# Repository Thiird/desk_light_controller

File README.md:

# Desk Controller

Desk controller is a gadget that connects to my pc and can:
- control a bias lighting system
- control a desk led strip

The bias lighting is the most complex part of this whole system.
The setup consists of a WS2815 12V led strip mounted around my main monitor, which is controlled by the STM32C0 of the desk controller by bit-banging the RGB data.
The RGB data is computed by a Visual C++ application running on windows and sent to the desk controller via serial port.
The main challenge here was to make a fast enough algorithm to to compute the RGB data, for the bias lighting to be reactive I wanted to achieve a 30Hz refresh rate of the RGB data, which means updating the leds color at most every 0.33.. seconds.
Without getting into GPU shaders and such, the wastest way to capture a screenshot of the screen and calculate the average color for the sections of the screen around the border, was to use the Desktop Duplication Windows API.

I inted too use this feature only during gaming or watching films, which I only do on windows. A Linux-equivalent application can always be made at a later moment,

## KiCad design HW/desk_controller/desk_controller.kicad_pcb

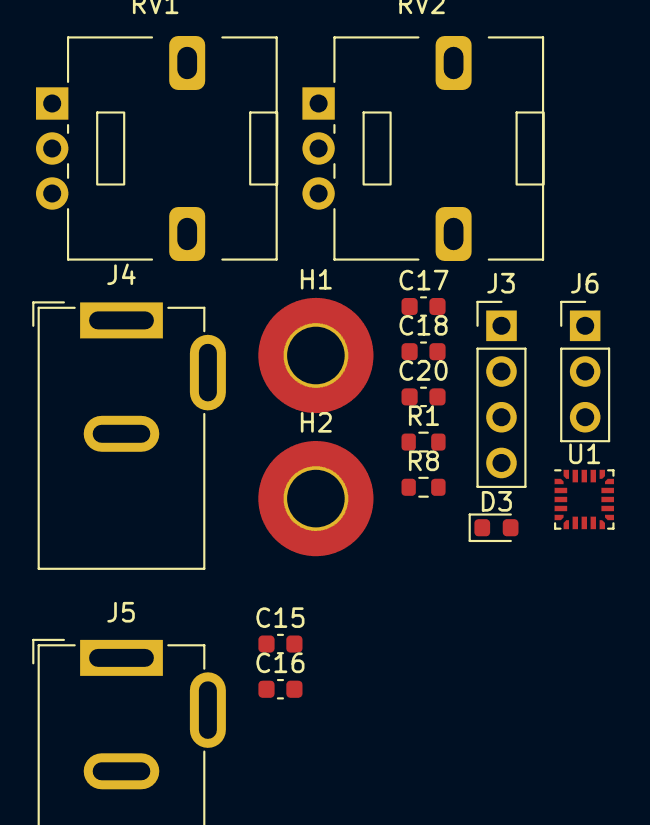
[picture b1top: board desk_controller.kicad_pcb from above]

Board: 2 copper layers, 17 parts (0 on the bottom side), 6 nets, no tracks yet.

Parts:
C15, C17, C18: 100n; C_0603_1608Metric
C16: 330n; C_0603_1608Metric
C20: 4u7; C_0603_1608Metric
D3: RED; LED_0603_1608Metric
H1, H2: MountingHole; MountingHole_3.2mm_M3_Pad_TopBottom
J3: SWD_header; PinHeader_1x04_P2.54mm_Vertical
J4, J5: Barrel_Jack_MountingPin; BarrelJack_GCT_DCJ200-10-A_Horizontal
J6: debug_uart; PinHeader_1x03_P2.54mm_Vertical
R1: 3k3; R_0603_1608Metric
R8: 10k; R_0603_1608Metric
RV1, RV2: R_Potentiometer; Potentiometer_Alps_RK09L_Single_Vertical
U1: STM32C011F4Ux; ST_UFQFPN-20_3x3mm_P0.5mm

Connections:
+3V3: C17.1, C20.1, J3.1, U1.2 (VDD)
+12V: C16.1, J4.1, J5.1
/mcu/NRST: C18.1, U1.4 (PF2)
GND: C15.2, C16.2, C17.2, C18.2, C20.2, D3.1 (K), J3.4, J5.2, J6.3, R8.2, U1.3 (VSS)
unnamed: D3.2 (A), R1.2
unnamed: R1.1, U1.19 (PB7)
